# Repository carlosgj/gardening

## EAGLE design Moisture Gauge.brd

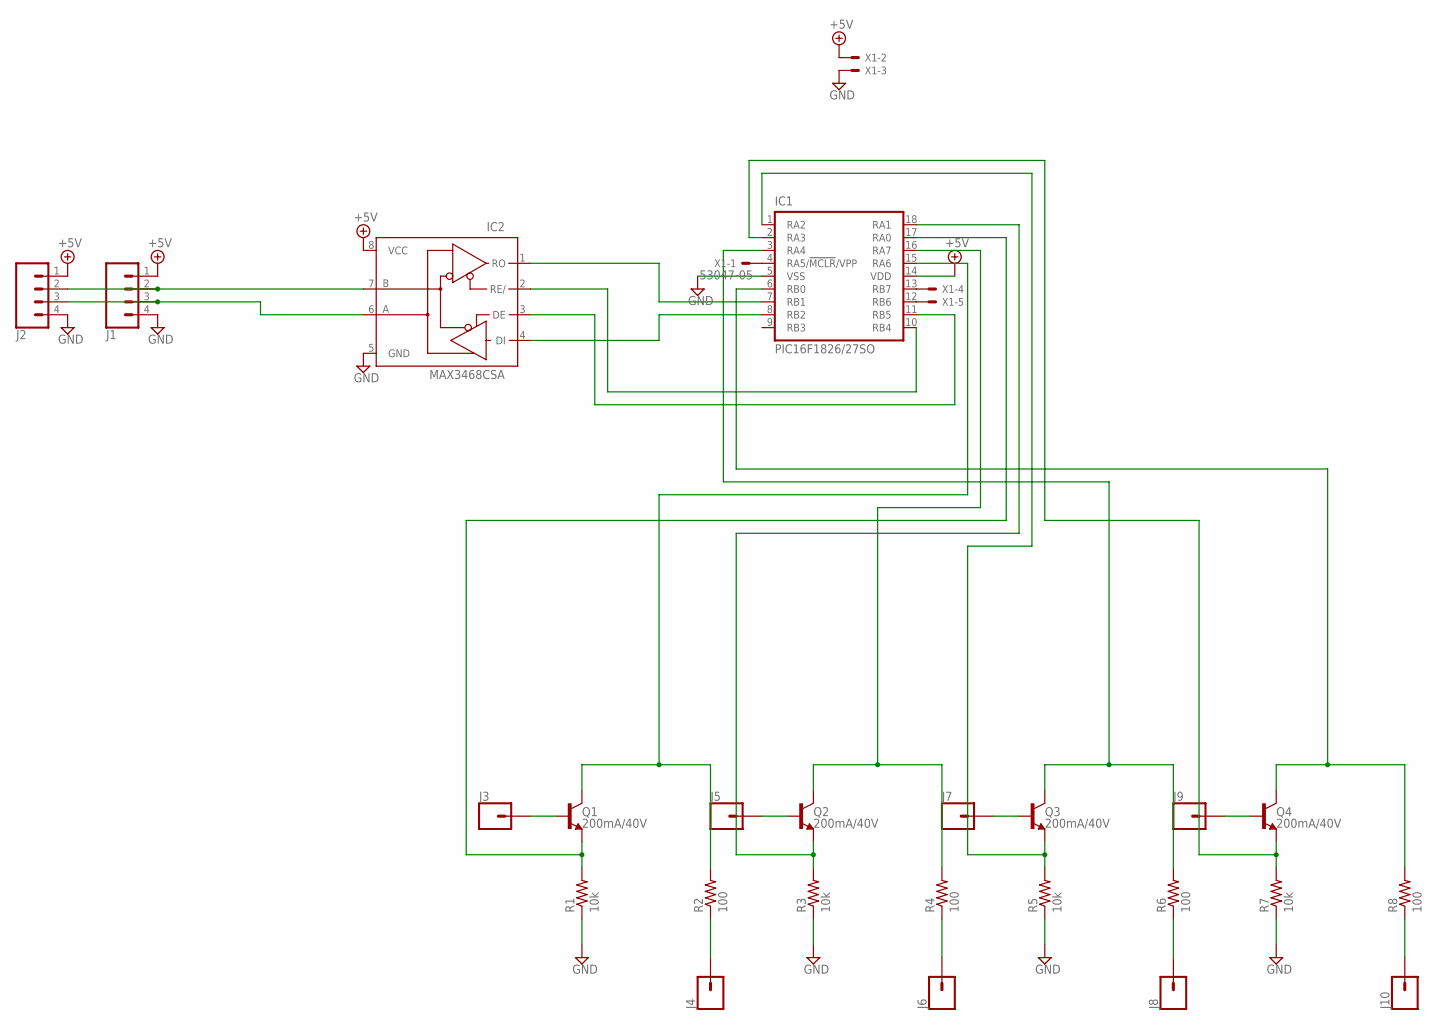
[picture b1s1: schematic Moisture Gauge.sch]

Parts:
IC1: PIC16F1826/27SO; SO-18W
IC2: MAX3468CSA; SO08
J1, J2: CONN_04SCREW; SCREWTERMINAL-3.5MM-4
J3, J4, J5, J6, J7, J8, J9, J10: CONN_01PTH_2MM; 1X01_2MM
Q1, Q2, Q3, Q4: 200mA/40V; TO-92
R1, R3, R5, R7: 10k; M1206
R2, R4, R6, R8: 100; M1206
X1: 53047-05

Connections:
+5V: IC1.14 (VDD), IC2.8 (VCC), J1.1, J2.1, X1.2
GND: IC1.5 (VSS), IC2.5 (GND), J1.4, J2.4, R1.1, R3.1, R5.1, R7.1, X1.3
unnamed: IC1.17 (RA0), Q1.1 (E), R1.2
unnamed: IC1.18 (RA1), Q2.1 (E), R3.2
unnamed: IC1.15 (RA6), Q1.3 (C), R2.2
unnamed: IC1.3 (RA4), Q3.3 (C), R6.2
unnamed: IC1.1 (RA2), Q3.1 (E), R5.2
unnamed: IC1.6 (RB0), Q4.3 (C), R8.2
unnamed: IC1.2 (RA3), Q4.1 (E), R7.2
unnamed: IC1.11 (RB5), IC2.3 (DE)
unnamed: IC2.7 (B), J1.2, J2.2
unnamed: IC2.6 (A), J1.3, J2.3
unnamed: IC1.7 (RB1), IC2.1 (RO)
unnamed: IC1.8 (RB2), IC2.4 (DI)
unnamed: IC1.10 (RB4), IC2.2 (RE/)
unnamed: IC1.4 (RA5/!MCLR!/VPP), X1.1
unnamed: IC1.13 (RB7), X1.4
unnamed: IC1.12 (RB6), X1.5
unnamed: IC1.16 (RA7), Q2.3 (C), R4.2
P1A: J3.1, Q1.2 (B)
P1B: J4.1, R2.1
P2A: J5.1, Q2.2 (B)
P2B: J6.1, R4.1
P3A: J7.1, Q3.2 (B)
P3B: J8.1, R6.1
P4A: J9.1, Q4.2 (B)
P4B: J10.1, R8.1

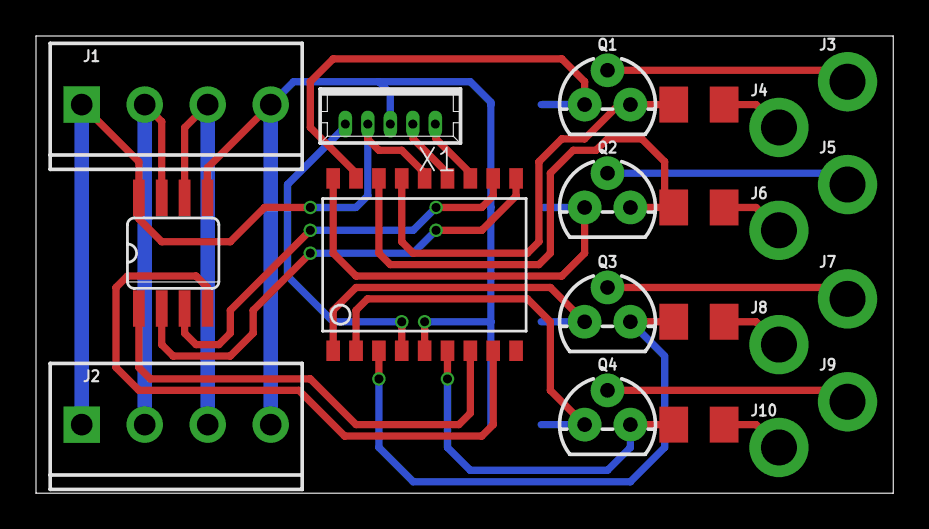
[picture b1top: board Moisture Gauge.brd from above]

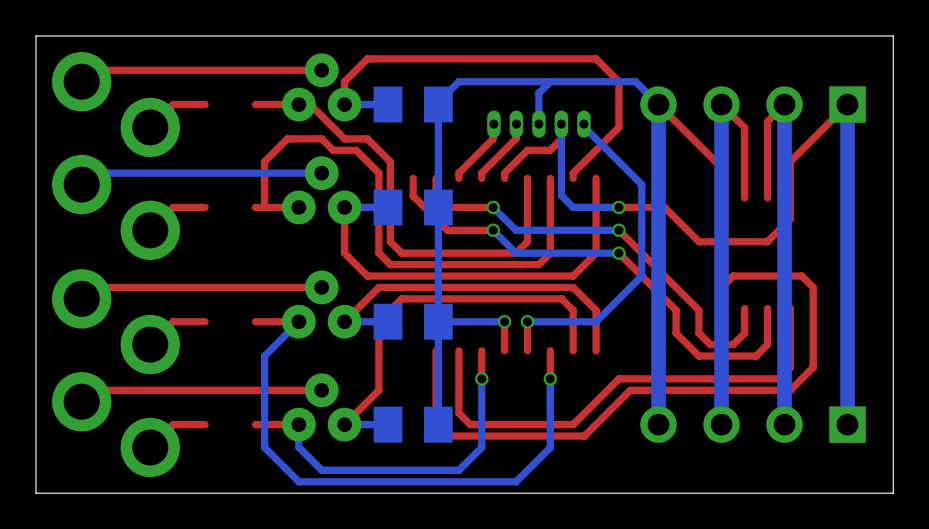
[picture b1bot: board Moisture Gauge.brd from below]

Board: 2 copper layers, 47.6 x 25.4 mm, 25 parts (4 on the bottom side), 27 nets.

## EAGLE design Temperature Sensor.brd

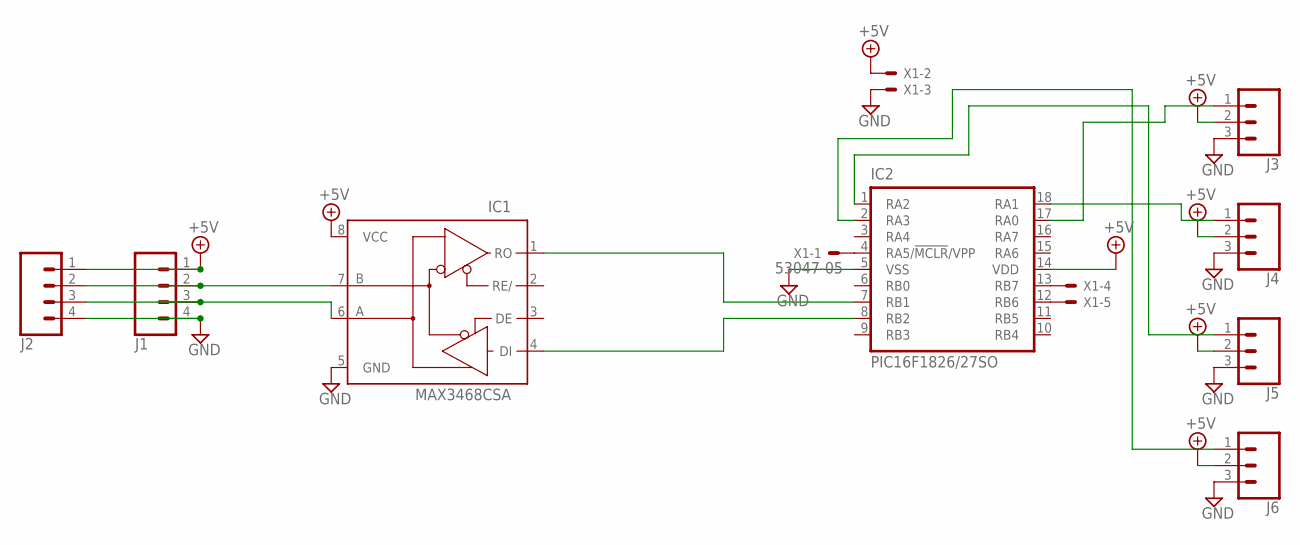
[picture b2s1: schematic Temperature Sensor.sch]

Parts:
IC1: MAX3468CSA; SO08
IC2: PIC16F1826/27SO; SO-18W
J1, J2: CONN_04SCREW; SCREWTERMINAL-3.5MM-4
J3, J4, J5, J6: CONN_03; 1X03
X1: 53047-05

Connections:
+5V: IC1.8 (VCC), IC2.14 (VDD), J1.1, J2.1, J3.2, J4.2, J5.2, J6.2, X1.2
GND: IC1.5 (GND), IC2.5 (VSS), J1.4, J2.4, J3.3, J4.3, J5.3, J6.3, X1.3
unnamed: IC1.1 (RO), IC2.7 (RB1)
unnamed: IC1.4 (DI), IC2.8 (RB2)
unnamed: IC2.4 (RA5/!MCLR!/VPP), X1.1
unnamed: IC2.13 (RB7), X1.4
unnamed: IC2.12 (RB6), X1.5
unnamed: IC1.7 (B), J1.2, J2.2
unnamed: IC1.6 (A), J1.3, J2.3
unnamed: IC2.17 (RA0), J3.1
unnamed: IC2.18 (RA1), J4.1
unnamed: IC2.1 (RA2), J5.1
unnamed: IC2.2 (RA3), J6.1

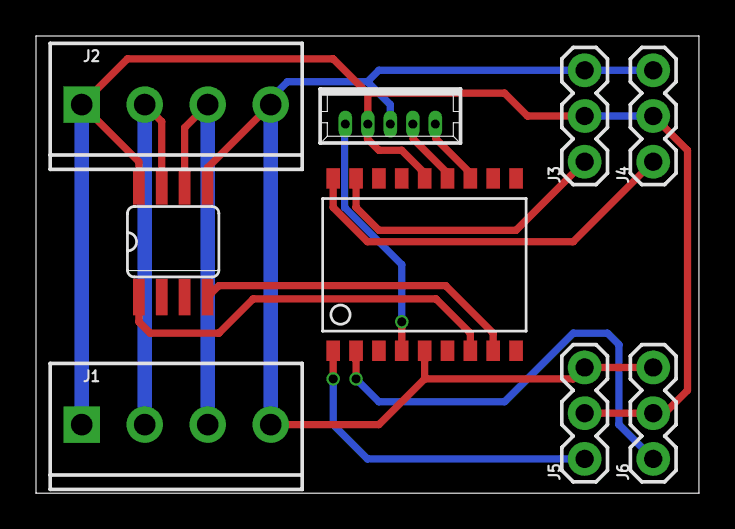
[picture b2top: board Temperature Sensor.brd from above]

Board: 2 copper layers, 36.8 x 25.4 mm, 9 parts (0 on the bottom side), 13 nets.

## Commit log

2018-06-03 Initial boards

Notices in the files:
parts and their libraries:
SparkFun-Connectors: Licensing: Creative Commons ShareAlike 4.0 International - https://creativecommons.org/licenses/by-sa/4.0
